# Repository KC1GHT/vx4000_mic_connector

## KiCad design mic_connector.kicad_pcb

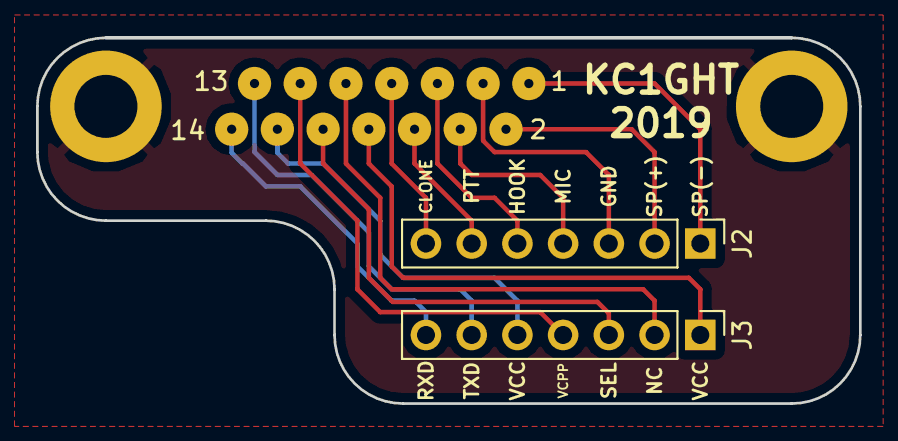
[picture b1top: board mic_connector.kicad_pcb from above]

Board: 2 copper layers, 45.7 x 20.3 mm, 5 parts (0 on the bottom side), 15 nets.

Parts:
J1: Conn_01x14_Male; ZIP-14
J2, J3: Conn_01x07_Male; Pin_Header_Straight_1x07_Pitch2.54mm
MH1, MH2: MountingHole_Pad; MountingHole_5.3mm_M5_Pad

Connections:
CLONE: J1.7, J2.7
Earth: MH1.1, MH2.1
GND: J1.3, J2.3
HOOK: J1.5, J2.5
MIC: J1.4, J2.4
NC: J1.9, J3.2
PTT: J1.6, J2.6
RESET: J1.12, J3.5
RXD: J1.14, J3.7
SEL: J1.10, J3.3
SP(+): J1.2, J2.2
SP(-): J1.1, J2.1
TXD: J1.13, J3.6
VCC: J1.8, J3.1
VCPP: J1.11, J3.4

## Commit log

2020-02-29 Added KiCAD files
